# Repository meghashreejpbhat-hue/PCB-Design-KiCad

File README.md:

# PCB-Design-KiCad
A collection of PCB design mini-projects completed using KiCad as part of my Value Added Course on PCB Design.

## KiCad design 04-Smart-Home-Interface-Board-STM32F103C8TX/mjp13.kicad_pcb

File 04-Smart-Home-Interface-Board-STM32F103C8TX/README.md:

# Smart Home Interface Board Using STM32F103C8TX

PCB design project developed using KiCad as part of my Value Added Course on PCB Design.

## Tools Used

- KiCad
- STM32F103C8TX
- Schematic Design
- PCB Layout
- 3D PCB Visualization

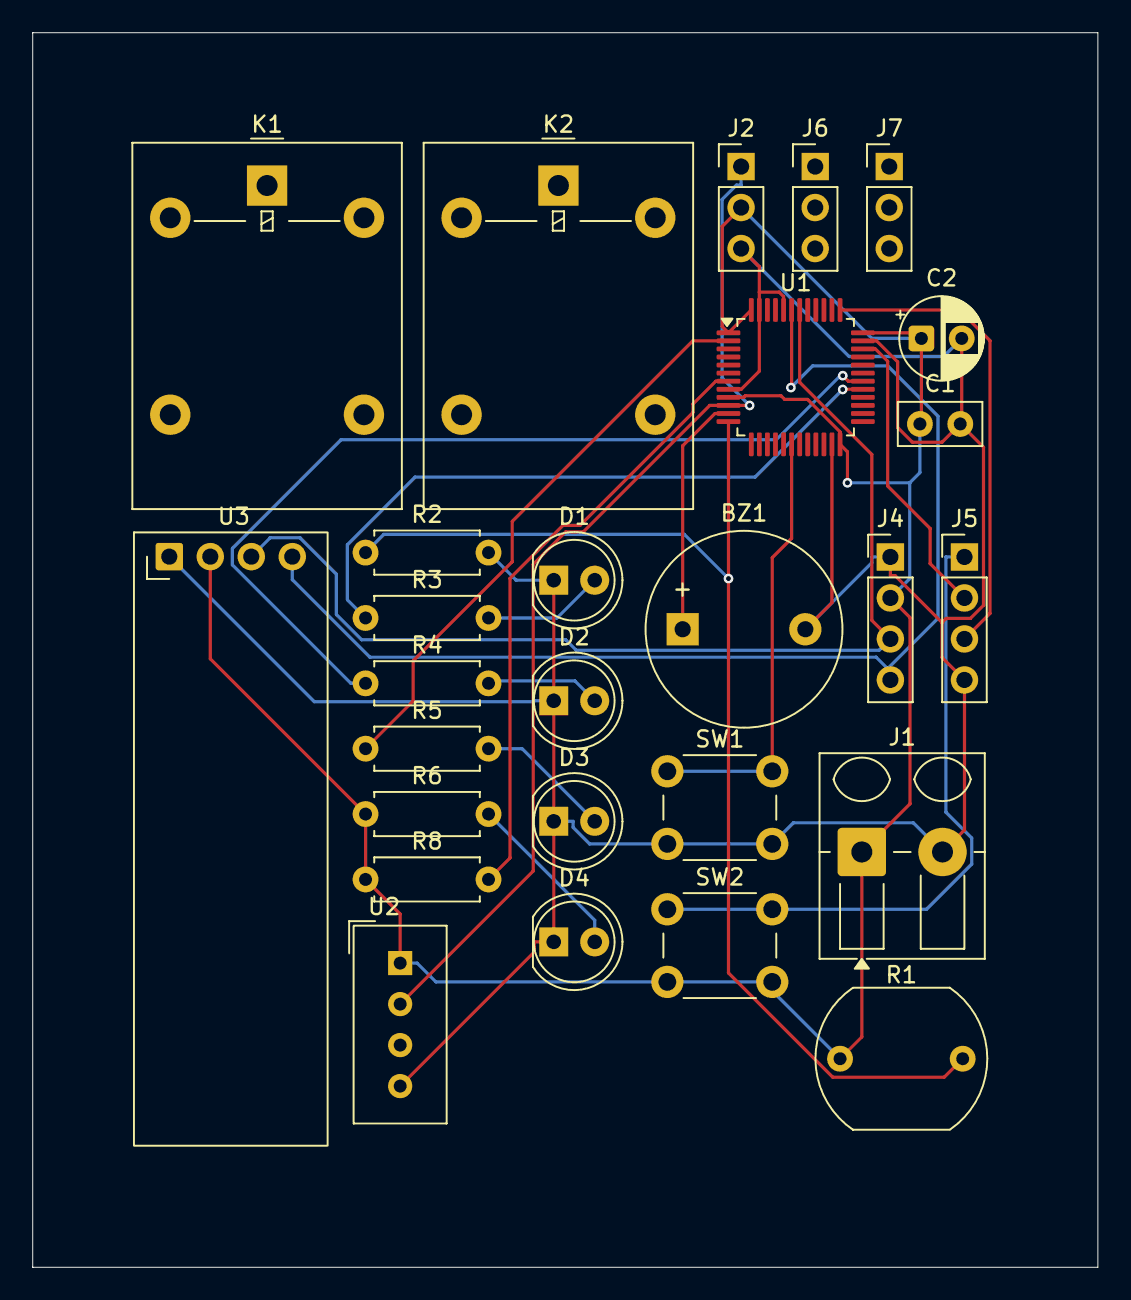
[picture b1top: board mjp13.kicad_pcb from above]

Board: 2 copper layers, 66.0 x 76.5 mm, 27 parts (0 on the bottom side), 19 nets.

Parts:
BZ1: Buzzer; Buzzer_12x9.5RM7.6
C1: C; C_Disc_D5.0mm_W2.5mm_P2.50mm
C2: C_Polarized; CP_Radial_D5.0mm_P2.50mm
D1, D2, D3, D4: LED; LED_D5.0mm
J1: Screw_Terminal_01x02; Altech_AK300_1x02_P5.00mm_45-Degree
J2, J6, J7: Conn_01x03_Pin; PinHeader_1x03_P2.54mm_Vertical
J4, J5: Conn_01x04_Pin; PinHeader_1x04_P2.54mm_Vertical
K1, K2: Relay_SPDT; Relay_SPDT_Omron-G5LE-1
R1: LDR03; R_LDR_10x8.5mm_P7.6mm_Vertical
R2, R3, R4, R5, R6, R8: R; R_Axial_DIN0207_L6.3mm_D2.5mm_P7.62mm_Horizontal
SW1, SW2: SW_Push; SW_PUSH_6mm
U1: STM32F103C8Tx; LQFP-48_7x7mm_P0.5mm
U2: DHT11; Aosong_DHT11_5.5x12.0_P2.54mm
U3: ER_OLEDM0.91_1x-I2C

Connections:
+3.3V: C1.1, C2.1, J1.1, J2.2, J4.2, R1.1, R6.1, R8.1, SW2.2, U1.1 (VBAT), U1.9 (VDDA), U1.24 (VDD), U1.36 (VDD), U1.48 (VDD), U2.1 (VDD), U3.2 (VCC)
GND: BZ1.2 (-), C1.2, C2.2, D1.1 (K), D2.1 (K), D3.1 (K), D4.1 (K), J1.2, J2.3, J4.1, J5.4, R2.2, SW1.2, U1.8 (VSSA), U1.23 (VSS), U1.35 (VSS), U1.44 (BOOT0), U1.47 (VSS), U2.4 (GND), U3.1 (GND)
unnamed: BZ1.1 (+), U1.11 (PA1)
unnamed: D1.2 (A), R3.2
unnamed: D2.2 (A), R4.2
unnamed: D3.2 (A), R5.2
unnamed: D4.2 (A), R6.2
unnamed: J2.1, U1.10 (PA0), U2.2 (DATA)
unnamed: J4.3, U1.42 (PB6), U3.3 (SCL)
unnamed: J4.4, U1.43 (PB7), U3.4 (SDA)
unnamed: J5.1, SW2.1
unnamed: J5.2, U1.34 (PA13)
unnamed: J5.3, U1.37 (PA14)
unnamed: R8.2, U1.7 (NRST)
unnamed: R1.2, R2.1, U1.12 (PA2)
unnamed: R3.1, U1.29 (PA8)
unnamed: R4.1, U1.30 (PA9)
unnamed: SW1.1, U1.18 (PB0)
unnamed: R5.1, U1.2 (PC13)

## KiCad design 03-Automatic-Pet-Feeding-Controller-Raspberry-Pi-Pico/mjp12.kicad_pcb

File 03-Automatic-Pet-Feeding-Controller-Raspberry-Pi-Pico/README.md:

# Automatic Pet Feeding Controller Using Raspberry Pi Pico

PCB design project developed using KiCad as part of my Value Added Course on PCB Design.

## Tools Used

- KiCad
- Raspberry Pi Pico
- Schematic Design
- PCB Layout
- 3D PCB Visualization

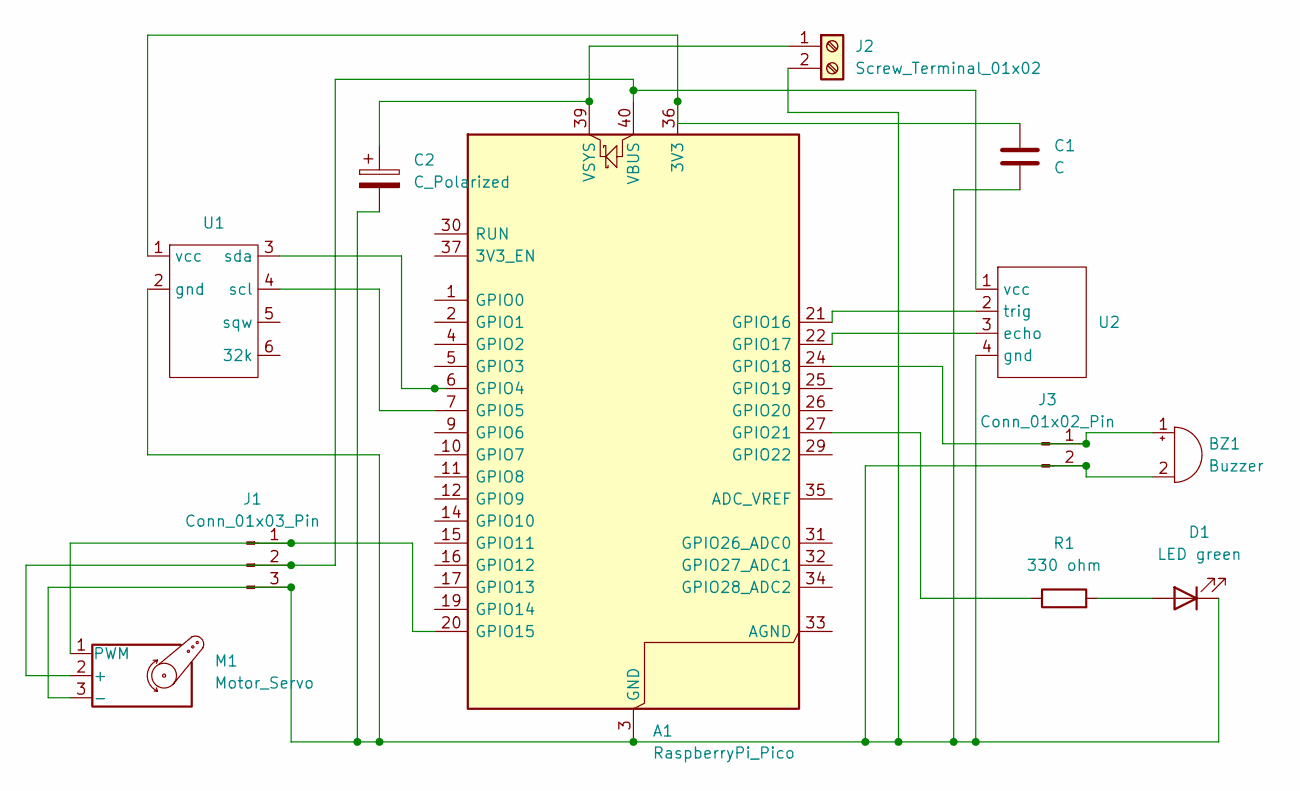
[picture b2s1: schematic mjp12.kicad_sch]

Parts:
A1: RaspberryPi_Pico; RaspberryPi_Pico_Common_Unspecified
BZ1: Buzzer; Buzzer_12x9.5RM7.6
C1: C; C_Disc_D5.0mm_W2.5mm_P5.00mm
C2: C_Polarized; CP_Radial_D5.0mm_P2.00mm
D1: LED green; LED_D5.0mm
J1: Conn_01x03_Pin; PinHeader_1x03_P2.54mm_Vertical
J2: Screw_Terminal_01x02; Altech_AK100_1x02_P5.00mm
J3: Conn_01x02_Pin; PinHeader_1x02_P2.54mm_Vertical
M1: Motor_Servo; PinHeader_1x03_P2.54mm_Vertical_SMD_Pin1Left
R1: 330 ohm; R_Axial_DIN0207_L6.3mm_D2.5mm_P10.16mm_Horizontal
U1: ds3231_rtc
U2: HCSO4

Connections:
unnamed: A1.36 (3V3), C1.1, U1.1 (vcc)
unnamed: A1.6 (GPIO4), U1.3 (sda)
unnamed: A1.7 (GPIO5), U1.4 (scl)
unnamed: A1.20 (GPIO15), J1.1, M1.1 (PWM)
unnamed: A1.21 (GPIO16), U2.2 (trig)
unnamed: A1.22 (GPIO17), U2.3 (echo)
unnamed: A1.24 (GPIO18), BZ1.1 (+), J3.1
unnamed: A1.27 (GPIO21), R1.1
unnamed: A1.40 (VBUS), J1.2, M1.2 (+), U2.1 (vcc)
unnamed: A1.39 (VSYS), C2.1, J2.1
unnamed: A1.3 (GND), A1.8 (GND), A1.13 (GND), A1.18 (GND), A1.23 (GND), A1.28 (GND), A1.38 (GND), BZ1.2 (-), C1.2, C2.2, D1.1 (K), J1.3, J2.2, J3.2, M1.3 (-), U1.2 (gnd), U2.4 (gnd)
unnamed: D1.2 (A), R1.2

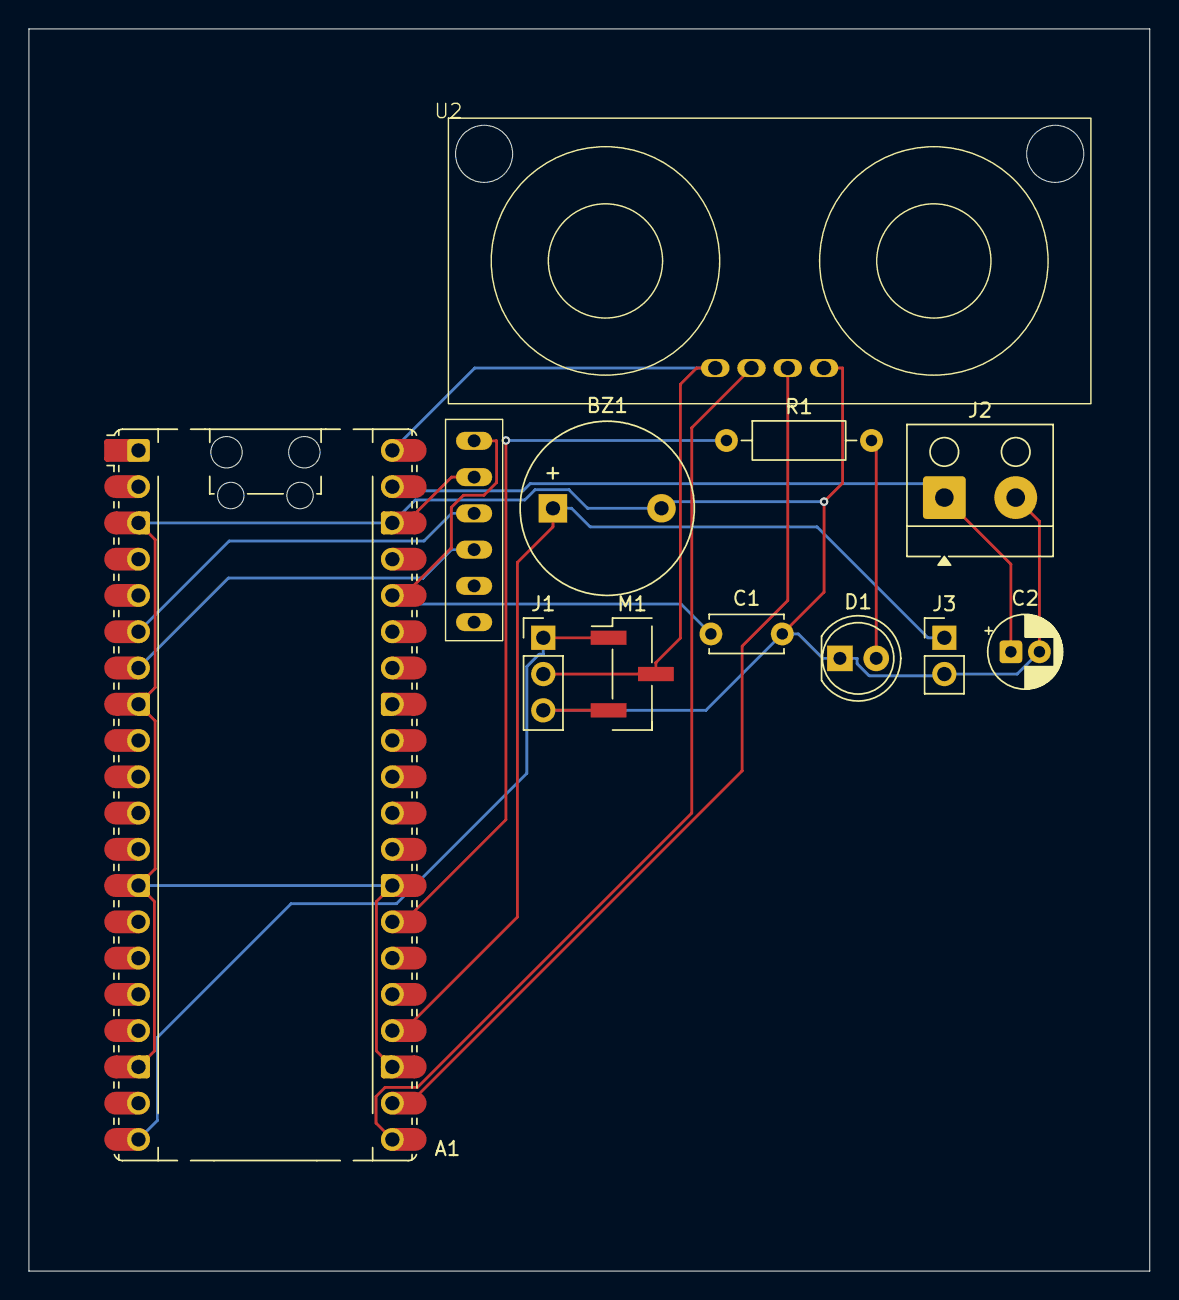
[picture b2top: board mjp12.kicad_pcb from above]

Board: 2 copper layers, 78.5 x 87.0 mm, 12 parts (0 on the bottom side), 12 nets.

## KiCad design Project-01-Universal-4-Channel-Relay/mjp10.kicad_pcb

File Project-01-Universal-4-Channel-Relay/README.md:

# Universal 4-Channel Relay Control Interface Board for Arduino

PCB design project developed using KiCad as part of my Value Added Course on PCB Design.

## Tools Used

- KiCad
- Schematic Design
- PCB Layout
- 3D PCB Visualization

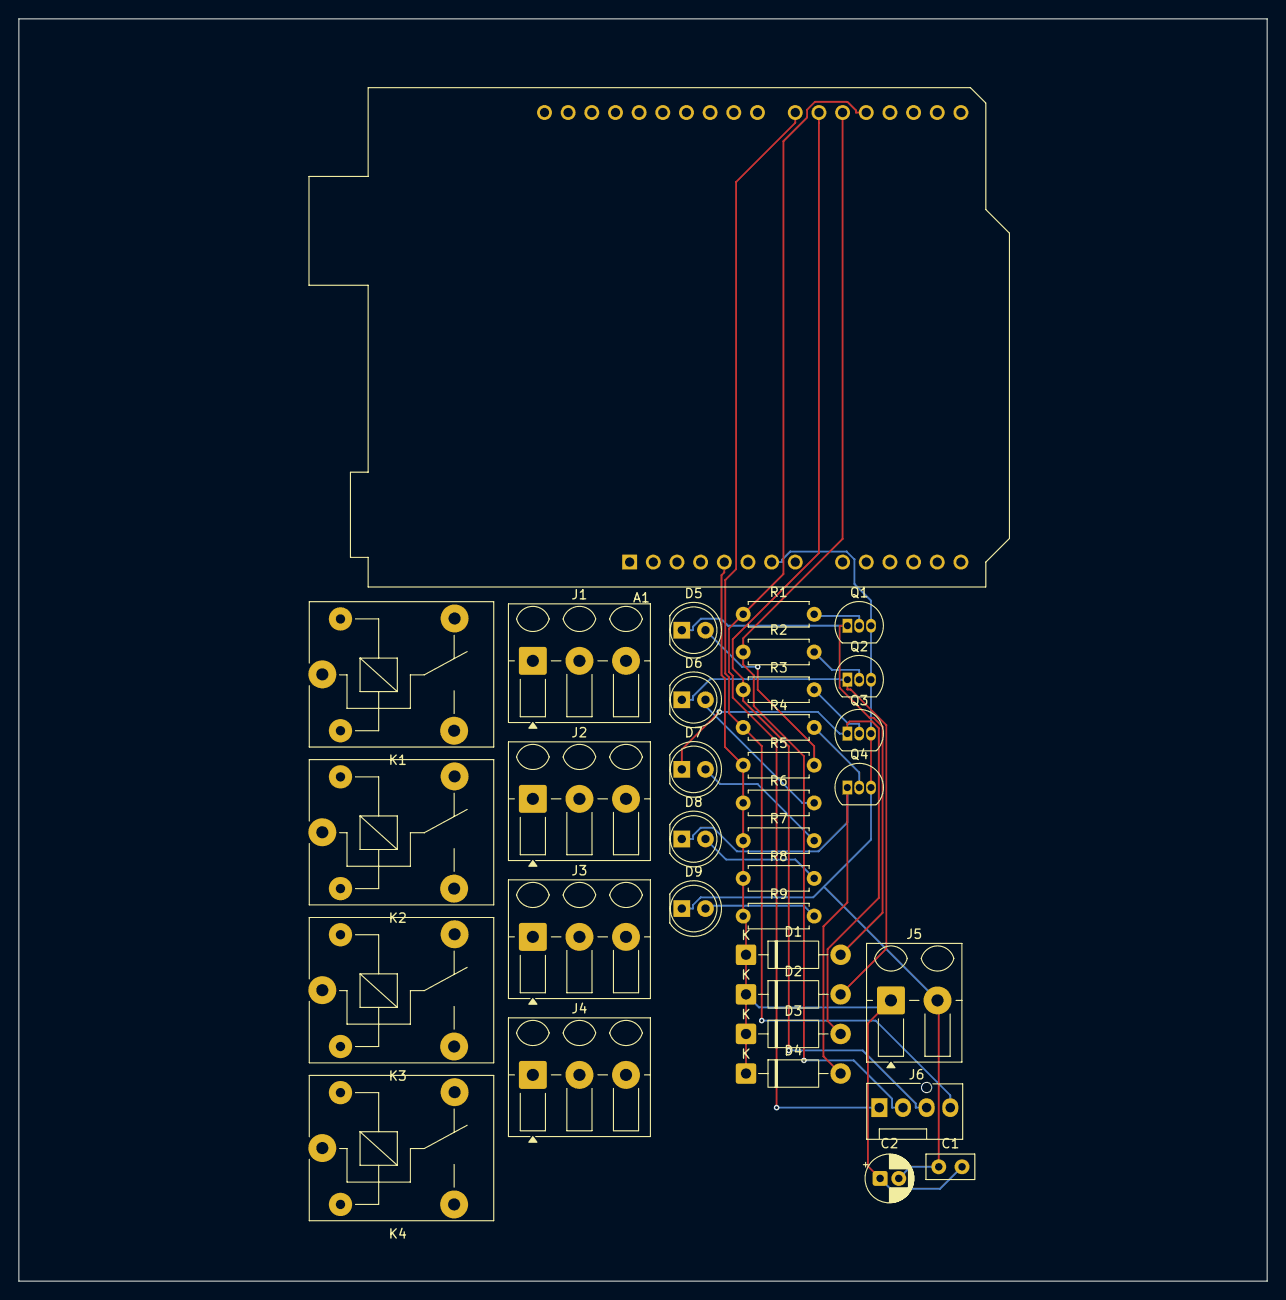
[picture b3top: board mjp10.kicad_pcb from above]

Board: 2 copper layers, 134.0 x 135.5 mm, 35 parts (0 on the bottom side), 19 nets.

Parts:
A1: Arduino_UNO_R3
C1: 100nF; C_Disc_D5.0mm_W2.5mm_P2.50mm
C2: C_Polarized; CP_Radial_D5.0mm_P2.00mm
D1, D2, D3, D4: D; D_DO-41_SOD81_P10.16mm_Horizontal
D5, D6, D7, D8: LED red; LED_D5.0mm
D9: LED green; LED_D5.0mm
J1, J2, J3, J4: Screw_Terminal_01x03; Altech_AK300_1x03_P5.00mm_45-Degree
J5: Screw_Terminal_01x02; Altech_AK300_1x02_P5.00mm_45-Degree
J6: Conn_01x04_Pin; FanPinHeader_1x04_P2.54mm_Vertical
K1, K2, K3, K4: Relay_SPDT; Relay_SPDT_SANYOU_SRD_Series_Form_C
Q1, Q2, Q3, Q4: BC547; TO-92_Inline
R1, R2, R3, R4: 1k ohm; R_Axial_DIN0207_L6.3mm_D2.5mm_P7.62mm_Horizontal
R5, R6, R7, R8, R9: 330 ohm; R_Axial_DIN0207_L6.3mm_D2.5mm_P7.62mm_Horizontal

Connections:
+5V: A1.5 (+5V), C1.2, C2.1, D1.1 (K), D2.1 (K), D3.1 (K), D4.1 (K), J5.1, R5.1, R6.1, R7.1, R8.1, R9.1
GND: A1.7 (GND), C1.1, C2.2, D9.1 (K), J5.2, Q1.3 (E), Q2.3 (E), Q3.3 (E), Q4.3 (E)
unnamed: A1.19 (D4), J6.1, R1.1
unnamed: A1.20 (D5), J6.2, R2.1
unnamed: A1.21 (D6), J6.3, R3.1
unnamed: A1.22 (D7), J6.4, R4.1
unnamed: D1.2 (A), D5.1 (K), Q1.1 (C)
unnamed: D2.2 (A), D6.1 (K), Q2.1 (C)
unnamed: D3.2 (A), D7.1 (K), Q3.1 (C)
unnamed: D4.2 (A), D8.1 (K), Q4.1 (C)
unnamed: D5.2 (A), R5.2
unnamed: D6.2 (A), R6.2
unnamed: D7.2 (A), R7.2
unnamed: D8.2 (A), R8.2
unnamed: D9.2 (A), R9.2
unnamed: Q1.2 (B), R1.2
unnamed: Q2.2 (B), R2.2
unnamed: Q3.2 (B), R3.2
unnamed: Q4.2 (B), R4.2
